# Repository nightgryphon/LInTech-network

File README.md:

# Проект по реконструкции сетевых плат ЛИнТех (IBM-PC, Корвет, УКНЦ, БК-0010)
Проект посвящен сбору информации, реконструкции и исследованию учебного сетевого комплекса LInTech для компьютерных классов СССР.

## История

Комплекс был [разработан](https://dic.academic.ru/dic.nsf/ruwiki/46187#.D0.9C.D0.BE.D0.B4.D0.B5.D1.80.D0.BD.D0.B8.D0.B7.D0.B0.D1.86.D0.B8.D1.8F) в 1990-х гг. ООО «ЛИнТех» («Лаборатория информационных технологий») совместно с ООО «Алтер-Вест»
для модернизации существующих учебных классов на базе ПЭВМ Корвет, УКНЦ и БК0010 для изучения современного на тот момент ПО для IBM PC.

Обеспечивалась работа мест учеников в режимах локальной сети и в терминальном режиме.

Наиболее интересным и необычным для того времени является **терминальный режим**, в котором существующие места учеников становятся сетевыми терминалами для головной машины на базе IBM PC. 
Поддерживаются как режимы текстового терминала для изучения MS DOS, так и графического для изучения MS Windows 3.11. 

В режиме локальной сети ученикам предоставляется доступ к дискам головной машины, причем скорость работы заметно выше штатной учебной сети. 

Комплекс упоминается в [журналах](http://school136.perm.ru/sunduk/samos/info.htm) и документах 
министерства образования и был [рекомендован](http://web.archive.org/web/20070927175919/http://www.informika.ru/text/goscom/normdoc/d_96/PRIK~5/l155.html) к применению в школах.
Однако классы на базе ПЭВМ СССР на тот момент уже активно замещались западными PC, в том числе при активной поддержке западных производителей, 
в результате комплекс LInTech не успел получить широкого распространения и был практически утрачен.

В настоящее время ученические платы изредка встречаются в ПЭВМ, списаных из школ. Чаще всего это ПЭВМ Корвет, реже УКНЦ, также известно несколько экземпляров плат для БК. 
Долгое время не удавалось разыскать сетевую плату и ПО головной машины, без которых невозможна работа ни одной из этих сетей. 
На данный момент доподлинно известно о двух сохранившихся экземплярах головной платы и, возможно, еще одном.

Первый и пока единственный публично упомянутый запуск-реконструкция сети LInTech / NET-Rt11 осуществлены [Arseny](http://uknc.narod.ru/) для ПЭВМ УКНЦ (МС 0511). 
На его сайте представлены [качественные фото плат](http://uknc.narod.ru/Img/index.htm) и [комплект учительского ПО для УКНЦ](http://uknc.narod.ru/Net-RT11/index.htm).
Однако задача реконструкции комплекса на данном этапе была существенно затруднена отсутствием копии защищенной от чтения прошивки микроконтроллера головной платы.

Второй экземпляр головной платы и бумажную документацию удалось разыскать [Serebriakov](https://github.com/paulargent). 
В 2020 году Serebriakov наладил контакты с директором ЛИнТех [Станиславом Кононовым](https://vk.com/id21313844), благодаря чему было получено сохранившееся в архивах ЛИнТех ПО и прошивки контроллера головной платы. Это решило принципиальный вопрос с прошивками и сделало возможной реконструкцию системы. Так же от Станислава было получено официальное разрешение на публикацию материалов в открытом доступе и дан зеленый свет проекту реконструкции плат.

[Night Gryphon](https://github.com/nightgryphon) удалось разыскать и восстановить клиентские платы БК0010 и УКНЦ, найти около десятка контроллеров от платы головной машины (увы, без самих плат).

Все это позволяет попробовать реконструировать и запустить сеть ЛИнТех.

## Реконструкция

Аппаратно комплекс реализован в виде клиентских плат, устанавливаемых в слоты расширения ПЭВМ учеников, и головной ISA платы для учительской IBM PC совместимой машины. 
Платы построены на основе микроконтроллеров Intel 8031 и 8051.

Связь в сети осуществляется по последовательной двухпроводной линии, что позволяет использовать существующую кабельную инфраструктуру компьютерных классов.

В качестве программного обеспечения были разработаны системы: 
- [NET-Rt11](https://www.emuverse.ru/wiki/%D0%A3%D0%9A%D0%9D%D0%A6_%D0%B6%D1%83%D1%80%D0%BD%D0%B0%D0%BB_1994-01_%D0%9B%D0%98%D0%BD%D0%A2%D0%B5%D1%85), 
- [DOS-Line](http://www.uw.ru/about/archive/dos-line/), 
- [NET-CP/M](https://oldkorvet.narod.ru/Utils.html)
- NET-БК0010

В данном проекте представлены:
- [Server-IBM-PC](./Server-IBM-PC/) - головная **[ учительская плата ISA для IBM PC ]** а так же **учительское ПО**
- [Terminal-UKNC](./Terminal-UKNC/) - клиентская плата УКНЦ
- [Terminal-BK0010](./Terminal-BK0010/) - клиентская плата БК 0010
- [Documentation](./Documentation/) - руководства

Дружественные проекты:
- [Терминал плата для ПЭВМ Корвет](https://github.com/lordamot/retro-lintech) была реконструирована коллегами NexusOfPenza и Lordamot

Платы в данном проекте не являются точной копией оригинала т.к. некоторые участки плат не видны под установлеными компонентами и невозможно сделать точную копию без разрушения оригинала. 
Реконструкция создана в KiCad с чистого листа имея оригинальную плату (или ее фото) в качестве образца. 
Не видимые элементы воссозданы путем отсмотра, прозвонки и изучения/воссоздания логики работы платы. 

Все данные публикуются с согласия представителя ЛИнТех.

## Ссылки
1. [academic.ru: Что такое УКНЦ? см раздел "Модернизация"](https://dic.academic.ru/dic.nsf/ruwiki/46187#.D0.9C.D0.BE.D0.B4.D0.B5.D1.80.D0.BD.D0.B8.D0.B7.D0.B0.D1.86.D0.B8.D1.8F)
2. [Каталог статей об УКНЦ (а также, о разработках фирмы ЛИнТех)](http://school136.perm.ru/sunduk/samos/info.htm)
3. [«NET-Rt11» — СЕТЕВАЯ СИСТЕМА ДЛЯ КУВТ «УКНЦ» С IBM-СОВМЕСТИМОЙ ГОЛОВНОЙ МАШИНОЙ](https://www.emuverse.ru/wiki/%D0%A3%D0%9A%D0%9D%D0%A6_%D0%B6%D1%83%D1%80%D0%BD%D0%B0%D0%BB_1994-01_%D0%9B%D0%98%D0%BD%D0%A2%D0%B5%D1%85)
4. [Приказ Мин Обр 'О модернизации отечественных КУВТ "Корвет" и УКНЦ' N 155/28 от 13.05.96г](http://web.archive.org/web/20070927175919/http://www.informika.ru/text/goscom/normdoc/d_96/PRIK~5/l155.html)
5. [Многозадачная, многопользовательская операционная система DOS-Line](http://www.uw.ru/about/archive/dos-line/)
6. [uknc.narod.ru: Фото от Arseny](http://uknc.narod.ru/Img/index.htm)
7. [uknc.narod.ru: оригиналы инструкции и ПО УКНЦ от Arseny](http://uknc.narod.ru/Net-RT11/index.htm)
8. [Старые фото и описание плат ЛИнТех от Serebriakov на форуме zx-pk.ru](https://zx-pk.ru/threads/2597?p=922488&viewfull=1#post922488)
9. [Образы дискет с установщиком ЛИнТех от Serebriakov на его старом сайте по Корвету oldkorvet.narod.ru)](https://oldkorvet.narod.ru/Utils.html)
10. [Дружественный проект по реконструкции платы для ПЭВМ Корвет от коллег NexusOfPenza и Lordamot](https://github.com/lordamot/retro-lintech)

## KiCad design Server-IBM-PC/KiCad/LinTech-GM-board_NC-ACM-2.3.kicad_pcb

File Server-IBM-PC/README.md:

# LInTech - плата Головной Машины (ГМ) - сервера IBM-PC

Платы реконструированы [Night Gryphon](https://night-gryphon.ru/vcard) по фото/сканам оригиналов плат, имеющихся в наличии у [Arseny](https://uknc.narod.ru/) (NC-ACM-2.2-1994) и [Serebriakov](https://github.com/PaulArgent) (NC-ACM-2.3E-1996).

В данный момент заказываются тестовые образцы платы 2.3.

Отдельное спасибо:
- [Arseny](https://uknc.narod.ru/) за исходные и дополнительные фото оригинальной платы версии NC-ACM-2.2-1994, отсмотр/поиск/прозвонку непонятных мест
- [Serebriakov](https://github.com/PaulArgent) за качественные сканы и дополнительные фото оригинальной платы версии NC-ACM-2.3E-1996.
- [Maxiol](https://forum.maxiol.com/) за помощь в воссоздании/проверке аналоговой части схемы
- Станиславу Масловски за опознание маркировки компонентов

Содержание:
- KiCad - проект реконструкции плат в формате KiCad
- LinTech-GM-board_NC-ACM-\*.pdf - реконструированые **схемы** плат 2.2 и 2.3Е
- Gerbers - **GERBER** файлы и **BOM** (списки компонентов) 
- Firmware - микропрограмма контроллера Intel 8051. Варианты для разных КУВТ и с разными лицензиями, см. README файлы.
- Reference_Photo - исходные фото, по которым велась реконструкция
- Cable - фото и схема соединительного кабеля
- [Software](./Software/) - **ПО головной машины**

Библиотека прошивок микроконтроллера платы и учительское ПО любезно предоставлены Станиславом Кононовым из ЛИнТех при содействии [Serebriakov](https://github.com/PaulArgent).

### Плата версии 2.2 
реконструирована по фото и с непосредственной помощью [Arseny](http://uknc.narod.ru/). 

### Плата версии 2.3Е
реконструирована по качественным сканам [Serebriakov](https://github.com/PaulArgent) и схеме платы 2.2. 

**Плата 2.3 имеет следующие отличия:**
- расширен блок перемычек выбора прерывания. Теперь доступны прерывания 3, 4, 7, 10, 11 (по умолчанию), 12
- светодиоды перенесены рядом с планкой и теперь видны снаружи корпуса РС, светодиод LD2 на линии "Reset" заменен на зеленый.
- добавлена возможность не запаивать не использовать часть аналоговой схемы. Добавлен подтягивающий резистор R8.
- Транзистор VT3 заменен на КТ646Б, изменены номиналы некоторых резисторов/конденсаторов.
- линия запроса прерывания вынесена из под кварцевого резонатора и добавлен земляной полигон.
- блоки перемычек заменены печатными джамперами в положении по умолчанию

На момент публикации реальные платы по данной реконструкции не изготавливались / не тестировались в железе, в проекте возможны неточности.

Реконструированые платы не являются точной копией оригинала. Положение дорожек и их форма, положение компонентов незначительно отличаются от оригинала т.к. рисовались с нуля в своей сетке с учетом современных возможностей производства и т.д. 

## Техническое описание
**[WIP]**

Плата построена на базе микроконтроллера Intel 8051 (ДД1).
 
ОЗУ контроллера расширено 573РУ10 (ДД4). Возможно размещение в этом ОЗУ как данных так и исполнение кода.
Возможна работа с микропрограммой во внешнем ПЗУ (ДД5) (требует проверки) после установки джампера Х5 в положение 2-3.

Адресное пространство контроллера разбито на 4 части по старшим битам адреса 14 и 15, что реализуется дешифратором ДД3:
- В старшей части 0xFххх расположен порт данных обмена с РС построеный на 1533ИР22 (ДД6, ДД7). 
- В адресах 0х4ххх расположено дополнительное ОЗУ
- В адресах 0х0ххх (предположительно) может быть установлено ПЗУ с внешней микропрограммой (ДД5)

При получении данных от РС в порт данных - выдается прерывание Int0 (триггер ДД13-А). Младший бит адреса порта данных, в который производилась запись, может быть прочитан из порта Р3 бит 4.

При чтении РС из порта данных выдается прерывание Int1 (триггер ДД13-Б)

Для запроса прерывания на РС необходимо записать "1" в порт Р3 бит 5.

При перезагрузке РС по сигналу RESET на шине ISA микроконтроллер так же переводится в ресет до снятия бита ресета со стороны РС записью "0" в бит 7 порта управления.

Обмен с линией осуществляется через последовательный порт RXD/TXD.

### Интерфейс PC
Базовый адрес портов В/В выбирается перемычками SA.1-7 которые соответствуют битам 3-9 адреса порта.

По умолчанию:
0x0120, 0х0121 - порт данных (Port 67: ДД6, ДД7)
0x0122 - порт статуса и управления (Port 89: ДД8, ДД9)

Чтение:
	3 - "1" = поступили данные от контроллера
	4 - "1" = порт данных свободен, данные прочитаны контроллером
	5 - контроллер выход T1/Port3.5
	6 - "1" = разрешено прерывание
	7 - перемычка SA.8

Запись
	6 - "1" = разрешить прерывание
	7 - ресет контроллера. После перезагрузки PC контроллер находится в ресете и надо записать "0" в этот бит для старта платы.

Прерывание 11 (может быть изменено перемычками IRQ) - выход MCU Port3 bit 4, со стороны PC разрешается записью "1" в бит 6 регистра управления.

Известные проблемы платы:
- при использовании прерывания ISA у некоторых экземпляров платы происходили его ложные срабатывания/помехи вплоть до "завешивания" РС. 
Предположительно связано с разводкой линии прерывания на плате версии 2.2. В плате версии 2.3 это было изменено.

### Описание микропрограммы
[Требуется помощь]

## Сетевой протокол
[Требуется помощь]

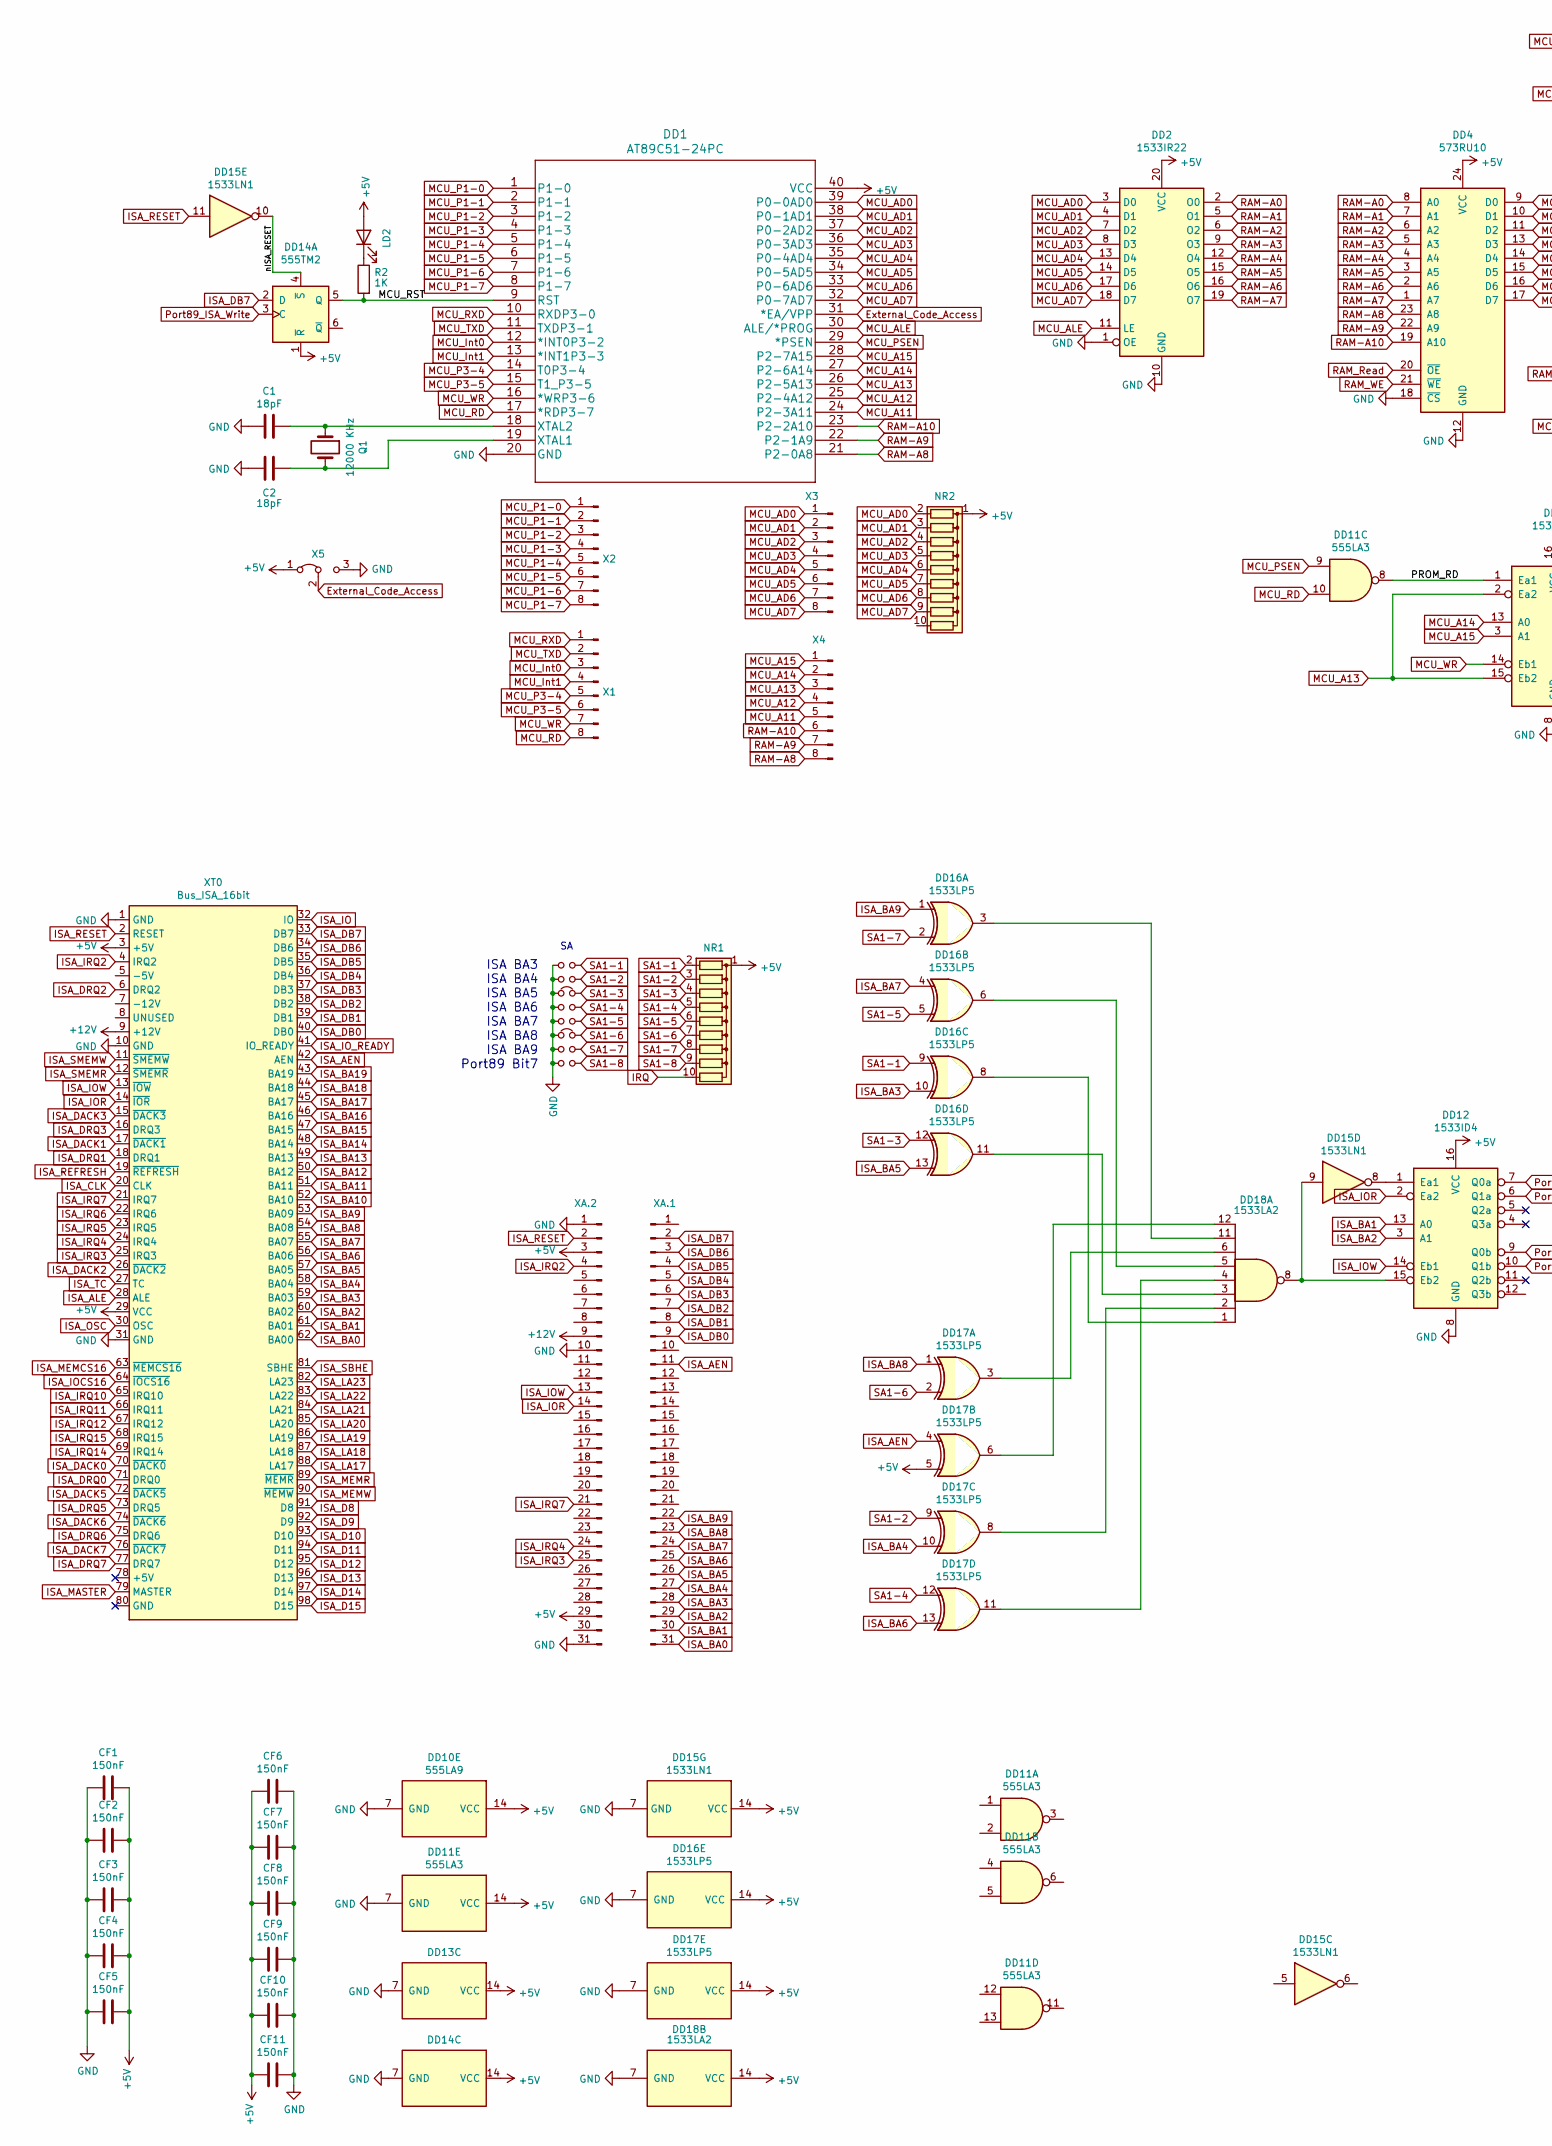
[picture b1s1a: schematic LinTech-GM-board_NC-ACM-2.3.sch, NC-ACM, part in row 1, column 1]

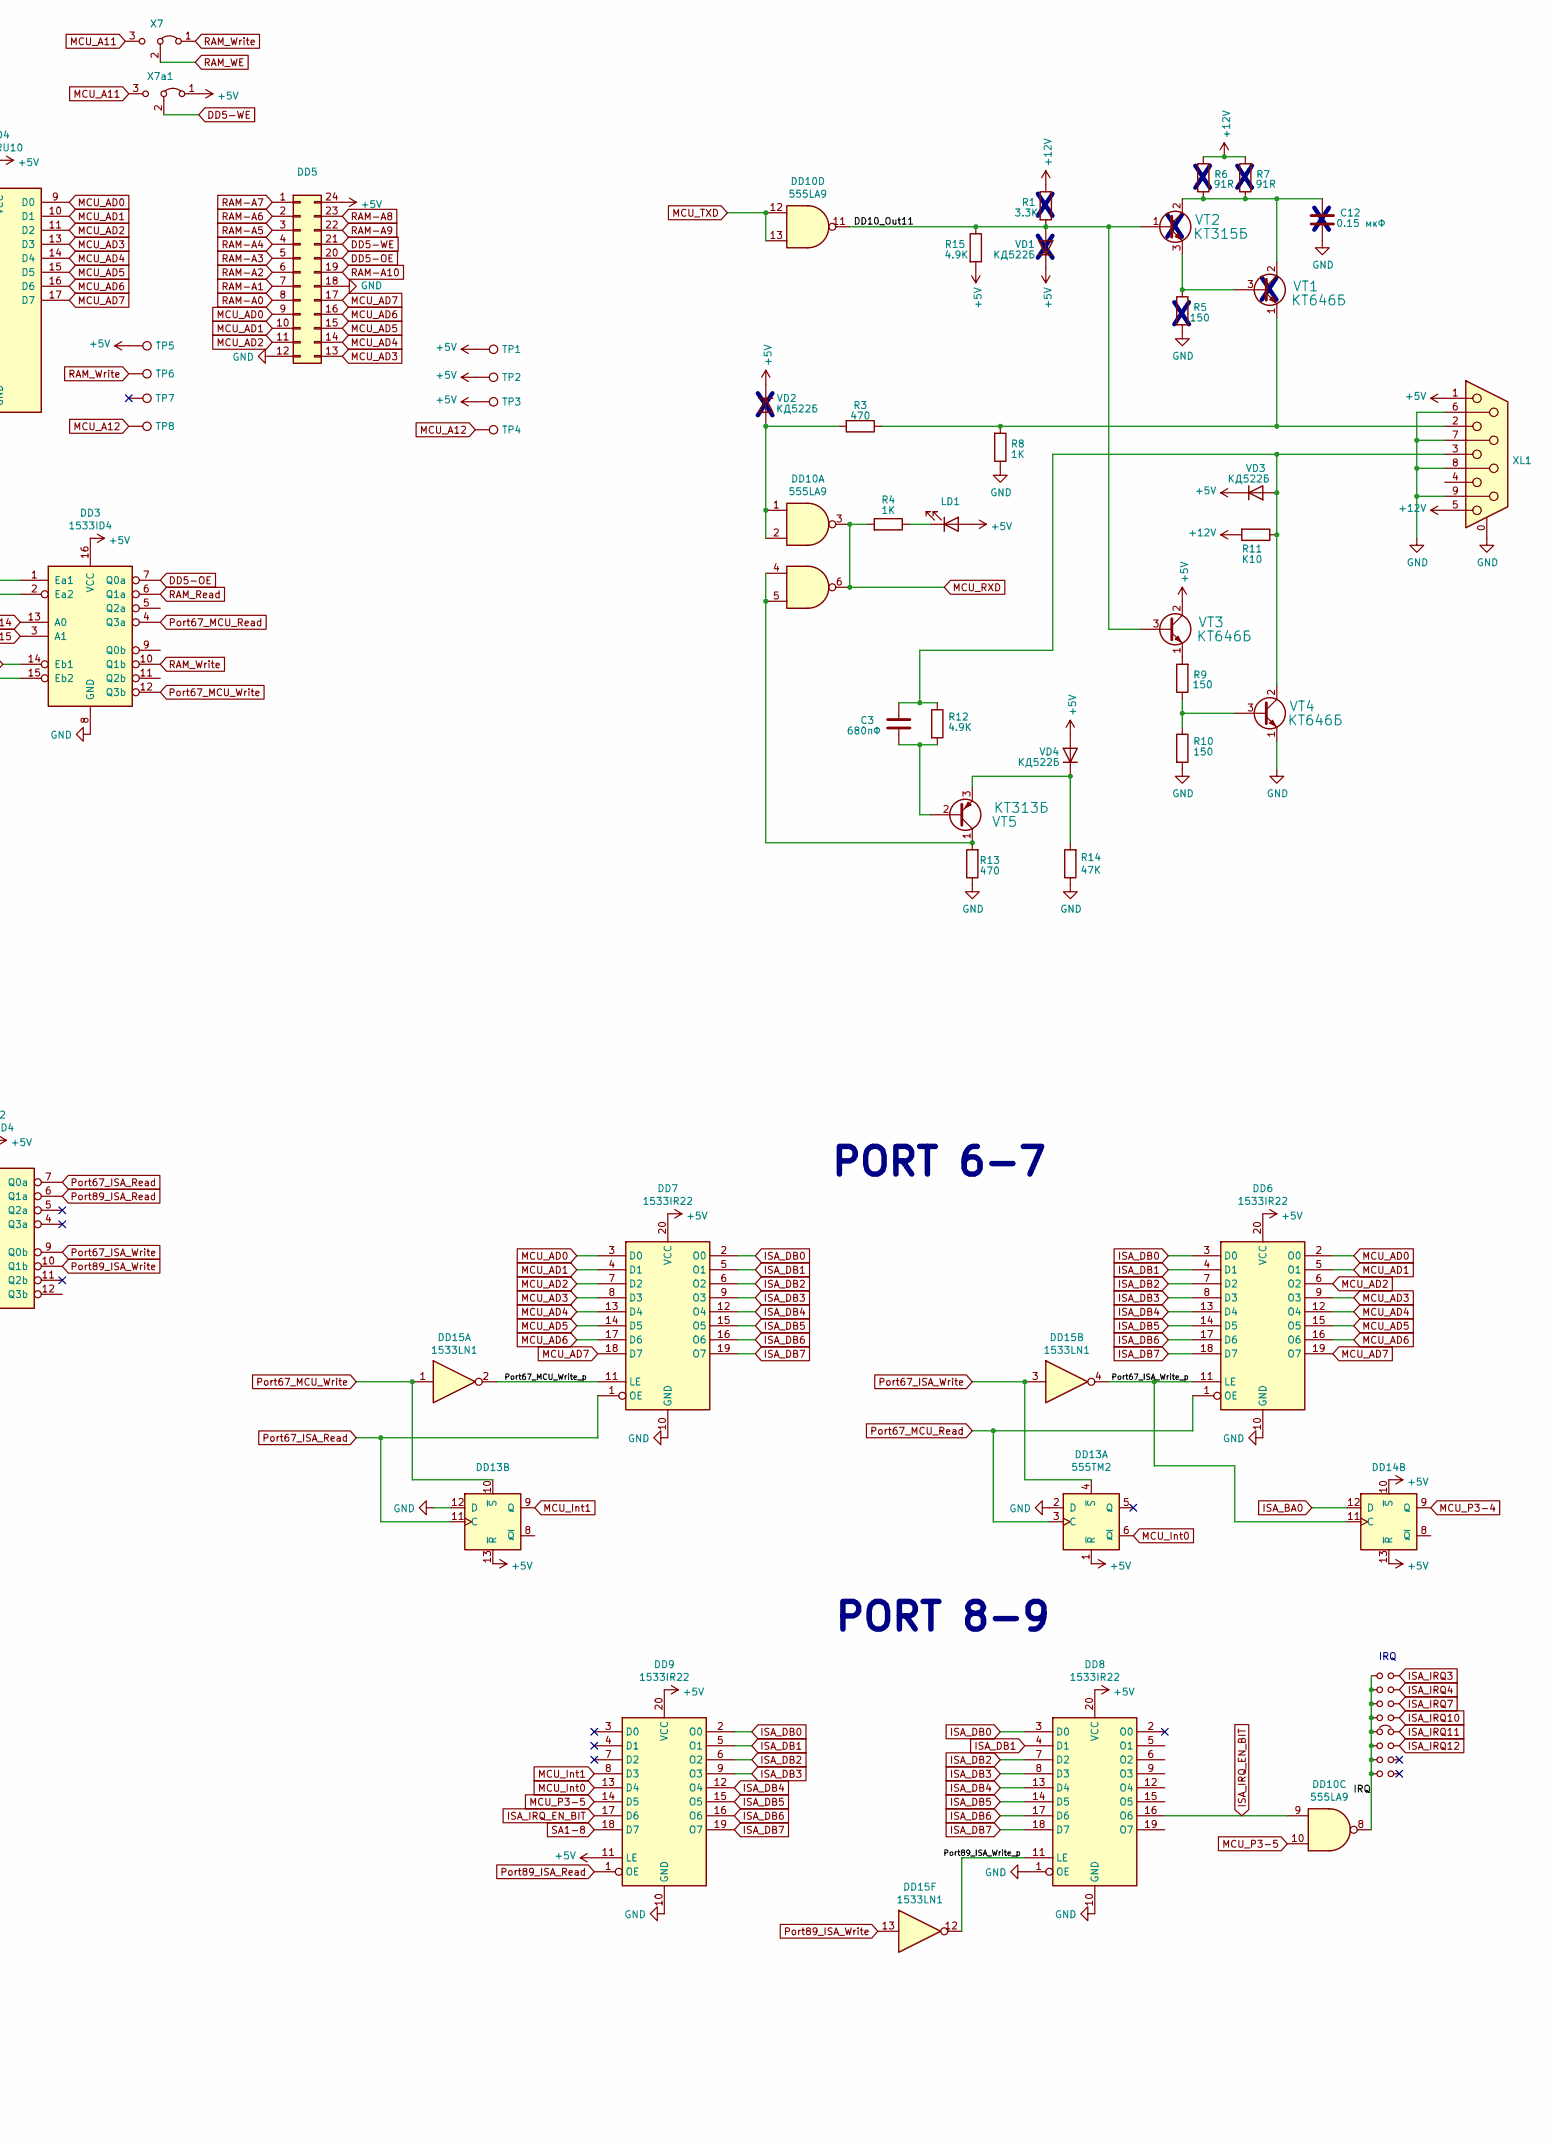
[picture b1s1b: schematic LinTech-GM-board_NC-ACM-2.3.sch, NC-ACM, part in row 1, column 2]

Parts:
C1, C2: 18pF; C_Disc_D5.0mm_W2.5mm_P5.00mm
C3: 680пФ; C_Disc_D5.0mm_W2.5mm_P5.00mm
C12: 0.15 мкФ; C_Disc_D5.0mm_W2.5mm_P5.00mm
CF1, CF2, CF3, CF4, CF5, CF6, CF7, CF8, CF9, CF10, CF11: 150nF; C_Disc_D5.0mm_W2.5mm_P5.00mm
DD1: AT89C51-24PC; DIP-40_W15.24mm
DD2, DD6, DD7, DD8, DD9: 1533IR22; DIP-20_W7.62mm
DD3, DD12: 1533ID4; DIP-16_W7.62mm
DD4: 573RU10; DIP-24_W15.24mm
DD5: Socket DIP24; DIP-24_W15.24mm_Socket
DD10: 555LA9; DIP-14_W7.62mm
DD11: 555LA3; DIP-14_W7.62mm
DD13, DD14: 555TM2; DIP-14_W7.62mm
DD15: 1533LN1; DIP-14_W7.62mm
DD16, DD17: 1533LP5; DIP-14_W7.62mm
DD18: 1533LA2; DIP-14_W7.62mm
LD1: LED Red 4mm; LED_D4.0mm
LD2: LED Green 4mm; LED_D4.0mm
NR1: 3.3K ?; R_Array_SIP10
NR2: R_Array_SIP10
Q1: 12000 KHz; Crystal_HC18-U_Horizontal
R1: 3.3K; R_Axial_DIN0309_L9.0mm_D3.2mm_P12.70mm_Horizontal
R2, R4, R8: 1K; R_Axial_DIN0309_L9.0mm_D3.2mm_P12.70mm_Horizontal
R3, R13: 470; R_Axial_DIN0309_L9.0mm_D3.2mm_P12.70mm_Horizontal
R5, R9, R10: 150; R_Axial_DIN0309_L9.0mm_D3.2mm_P12.70mm_Horizontal
R6, R7: 91R; R_Axial_DIN0918_L18.0mm_D9.0mm_P22.86mm_Horizontal
R11: K10; R_Axial_DIN0918_L18.0mm_D9.0mm_P22.86mm_Horizontal
R12, R15: 4.9K; R_Axial_DIN0309_L9.0mm_D3.2mm_P12.70mm_Horizontal
R14: 47K; R_Axial_DIN0309_L9.0mm_D3.2mm_P12.70mm_Horizontal
SAjp1, SAjp2, SAjp4, SAjp5, SAjp7, SAjp8, SAjp9, SAjp10, SAjp11, SAjp12, SAjp14, SAjp15, SAjp16: Jumper_P2.54mm_Open
SAjp3, SAjp6, SAjp13: Jumper_P2.54mm_Close
TP1, TP2, TP3, TP4, TP5, TP6, TP7, TP8: TestPoint; TestPad
VD1, VD2, VD3, VD4: КД522Б; D_A-405_P12.70mm_Horizontal
VT1, VT3, VT4: КТ646Б; TO-126-3_Vertical
VT2: КТ315Б; TO-92S_Wide
VT5: КТ313Б; TO-92
X1, X2, X3, X4: PinHeader_1x08_P2.54mm_Vertical
X5: PinHeader_1x03_P2.54mm_Vertical
X7, X7a1: Conn_02x03_Counter_Clockwise; Jumper3_12closed_P2.54mm
XA.1, XA.2: PinHeader_1x31_P2.54mm_Vertical
XL1: DB9_Female; DSUB-9_Female_Horizontal_P2.77x2.84mm_EdgePinOffset7.70mm_H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
XT0: Bus_ISA_16bit; BUS_AT

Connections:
+5V: CF1.2, CF2.1, CF3.2, CF4.2, CF5.1, CF6.2, CF7.2, CF8.1, CF9.2, CF10.2, CF11.2, DD1.40 (VCC), DD2.20 (VCC), DD3.16 (VCC), DD4.24 (VCC), DD5.24, DD6.20 (VCC), DD7.20 (VCC), DD8.20 (VCC), DD9.11 (LE), DD9.20 (VCC), DD10.14 (VCC), DD11.14 (VCC), DD12.16 (VCC), DD13.1 (~R), DD13.13 (~R), DD13.14 (VCC), DD14.1 (~R), DD14.10 (~S), DD14.13 (~R), DD14.14 (VCC), DD15.14 (VCC), DD16.14 (VCC), DD17.5, DD17.14 (VCC), DD18.14 (VCC), LD1.2 (A), LD2.2 (A), NR1.1 (common), NR2.1 (common), R15.2, TP1.1, TP2.1, TP3.1, TP5.1, VD1.1 (K), VD2.1 (K), VD3.1 (K), VD4.2 (A), VT3.2 (C), X5.1 (A), X7a1.1 (A), XA.2.3, XA.2.29, XL1.1, XT0.3 (+5V), XT0.29 (VCC)
+12V: R1.1, R6.2, R7.2, R11.2, XA.2.9, XL1.5, XT0.9 (+12V)
/DD10_Out11: DD10.11, R1.2, R15.1, VD1.2 (A), VT2.1 (B), VT3.3 (B)
/MCU_RST: DD1.9 (RST), DD14.5 (Q), R2.2
/PROM_RD: DD3.1 (Ea1), DD11.8
/Port67_ISA_Write_p: DD6.11 (LE), DD14.11 (C), DD15.4
/Port67_MCU_Write_p: DD7.11 (LE), DD15.2
/Port89_ISA_Write_p: DD8.11 (LE), DD15.12
/nISA_RESET: DD14.4 (~S), DD15.10
DD5-OE: DD3.7 (Q0a), DD5.20
DD5-WE: DD5.21, X7a1.2 (C)
External_Code_Access: DD1.31 (*EA/VPP), X5.2 (C)
GND: C1.2, C2.1, C12.2, CF1.1, CF2.2, CF3.1, CF4.1, CF5.2, CF6.1, CF7.1, CF8.2, CF9.1, CF10.1, CF11.1, DD1.20 (GND), DD2.1 (OE), DD2.10 (GND), DD3.8 (GND), DD4.12 (GND), DD4.18 (~CS), DD5.12, DD5.18, DD6.10 (GND), DD7.10 (GND), DD8.1 (OE), DD8.10 (GND), DD9.10 (GND), DD10.7 (GND), DD11.7 (GND), DD12.8 (GND), DD13.2 (D), DD13.7 (GND), DD13.12 (D), DD14.7 (GND), DD15.7 (GND), DD16.7 (GND), DD17.7 (GND), DD18.7 (GND), R5.2, R8.1, R10.2, R13.1, R14.1, SAjp1.1, SAjp2.1, SAjp3.1, SAjp4.1, SAjp5.1, SAjp6.1, SAjp7.1, SAjp8.1, VT4.1 (E), X5.3 (B), XA.2.1, XA.2.10, XA.2.31, XL1.0 (PAD), XL1.6, XL1.7, XL1.8, XL1.9, XT0.1 (GND), XT0.10 (GND), XT0.31 (GND)
IRQ: DD10.8, NR1.10 (R9), SAjp9.1, SAjp10.1, SAjp11.1, SAjp12.1, SAjp13.1, SAjp14.1, SAjp15.1, SAjp16.1
ISA_AEN: DD17.4, XA.1.11, XT0.42 (AEN)
ISA_ALE: XT0.28 (ALE)
ISA_BA0: DD14.12 (D), XA.1.31, XT0.62 (BA00)
ISA_BA1: DD12.13 (A0), XA.1.30, XT0.61 (BA01)
ISA_BA2: DD12.3 (A1), XA.1.29, XT0.60 (BA02)
ISA_BA3: DD16.10, XA.1.28, XT0.59 (BA03)
ISA_BA4: DD17.10, XA.1.27, XT0.58 (BA04)
ISA_BA5: DD16.13, XA.1.26, XT0.57 (BA05)
ISA_BA6: DD17.13, XA.1.25, XT0.56 (BA06)
ISA_BA7: DD16.4, XA.1.24, XT0.55 (BA07)
ISA_BA8: DD17.1, XA.1.23, XT0.54 (BA08)
ISA_BA9: DD16.1, XA.1.22, XT0.53 (BA09)
ISA_BA10: XT0.52 (BA10)
ISA_BA11: XT0.51 (BA11)
ISA_BA12: XT0.50 (BA12)
ISA_BA13: XT0.49 (BA13)
ISA_BA14: XT0.48 (BA14)
ISA_BA15: XT0.47 (BA15)
ISA_BA16: XT0.46 (BA16)
ISA_BA17: XT0.45 (BA17)
ISA_BA18: XT0.44 (BA18)
ISA_BA19: XT0.43 (BA19)
ISA_CLK: XT0.20 (CLK)
ISA_D8: XT0.91 (D8)
ISA_D9: XT0.92 (D9)
ISA_D10: XT0.93 (D10)
ISA_D11: XT0.94 (D11)
ISA_D12: XT0.95 (D12)
ISA_D13: XT0.96 (D13)
ISA_D14: XT0.97 (D14)
ISA_D15: XT0.98 (D15)
ISA_DACK0: XT0.70 (~DACK0)
ISA_DACK1: XT0.17 (~DACK1)
ISA_DACK2: XT0.26 (~DACK2)
ISA_DACK3: XT0.15 (~DACK3)
ISA_DACK5: XT0.72 (~DACK5)
ISA_DACK6: XT0.74 (~DACK6)
ISA_DACK7: XT0.76 (~DACK7)
ISA_DB0: DD6.3 (D0), DD7.2 (O0), DD8.3 (D0), DD9.2 (O0), XA.1.9, XT0.40 (DB0)
ISA_DB1: DD6.4 (D1), DD7.5 (O1), DD8.4 (D1), DD9.5 (O1), XA.1.8, XT0.39 (DB1)
ISA_DB2: DD6.7 (D2), DD7.6 (O2), DD8.7 (D2), DD9.6 (O2), XA.1.7, XT0.38 (DB2)
ISA_DB3: DD6.8 (D3), DD7.9 (O3), DD8.8 (D3), DD9.9 (O3), XA.1.6, XT0.37 (DB3)
ISA_DB4: DD6.13 (D4), DD7.12 (O4), DD8.13 (D4), DD9.12 (O4), XA.1.5, XT0.36 (DB4)
ISA_DB5: DD6.14 (D5), DD7.15 (O5), DD8.14 (D5), DD9.15 (O5), XA.1.4, XT0.35 (DB5)
ISA_DB6: DD6.17 (D6), DD7.16 (O6), DD8.17 (D6), DD9.16 (O6), XA.1.3, XT0.34 (DB6)
ISA_DB7: DD6.18 (D7), DD7.19 (O7), DD8.18 (D7), DD9.19 (O7), DD14.2 (D), XA.1.2, XT0.33 (DB7)
ISA_DRQ0: XT0.71 (DRQ0)
ISA_DRQ1: XT0.18 (DRQ1)
ISA_DRQ2: XT0.6 (DRQ2)
ISA_DRQ3: XT0.16 (DRQ3)
ISA_DRQ5: XT0.73 (DRQ5)
ISA_DRQ6: XT0.75 (DRQ6)
ISA_DRQ7: XT0.77 (DRQ7)
ISA_IO: XT0.32 (IO)
ISA_IOCS16: XT0.64 (~IOCS16)
ISA_IOR: DD12.2 (Ea2), XA.2.14, XT0.14 (~IOR)
ISA_IOW: DD12.14 (Eb1), XA.2.13, XT0.13 (~IOW)
ISA_IO_READY: XT0.41 (IO_READY)
ISA_IRQ2: XA.2.4, XT0.4 (IRQ2)
ISA_IRQ3: SAjp9.2, XA.2.25, XT0.25 (IRQ3)
ISA_IRQ4: SAjp10.2, XA.2.24, XT0.24 (IRQ4)
ISA_IRQ5: XT0.23 (IRQ5)
ISA_IRQ6: XT0.22 (IRQ6)
ISA_IRQ7: SAjp11.2, XA.2.21, XT0.21 (IRQ7)
ISA_IRQ10: SAjp12.2, XT0.65 (IRQ10)
ISA_IRQ11: SAjp13.2, XT0.66 (IRQ11)
ISA_IRQ12: SAjp14.2, XT0.67 (IRQ12)
ISA_IRQ14: XT0.69 (IRQ14)
ISA_IRQ15: XT0.68 (IRQ15)
ISA_IRQ_EN_BIT: DD8.16 (O6), DD9.17 (D6), DD10.9
ISA_LA17: XT0.88 (LA17)
ISA_LA18: XT0.87 (LA18)
ISA_LA19: XT0.86 (LA19)
ISA_LA20: XT0.85 (LA20)
ISA_LA21: XT0.84 (LA21)
ISA_LA22: XT0.83 (LA22)
ISA_LA23: XT0.82 (LA23)
ISA_MASTER: XT0.79 (MASTER)
ISA_MEMCS16: XT0.63 (~MEMCS16)
ISA_MEMR: XT0.89 (~MEMR)
ISA_MEMW: XT0.90 (~MEMW)
ISA_OSC: XT0.30 (OSC)
ISA_REFRESH: XT0.19 (~REFRESH)
ISA_RESET: DD15.11, XA.2.2, XT0.2 (RESET)
ISA_SBHE: XT0.81 (SBHE)
ISA_SMEMR: XT0.12 (~SMEMR)
ISA_SMEMW: XT0.11 (~SMEMW)
ISA_TC: XT0.27 (TC)
MCU_A11: DD1.24 (P2-3A11), X4.5, X7.3 (B), X7a1.3 (B)
MCU_A12: DD1.25 (P2-4A12), TP4.1, TP8.1, X4.4
MCU_A13: DD1.26 (P2-5A13), DD3.2 (Ea2), DD3.15 (Eb2), X4.3
MCU_A14: DD1.27 (P2-6A14), DD3.13 (A0), X4.2
MCU_A15: DD1.28 (P2-7A15), DD3.3 (A1), X4.1
MCU_AD0: DD1.39 (P0-0AD0), DD2.3 (D0), DD4.9 (D0), DD5.9, DD6.2 (O0), DD7.3 (D0), NR2.2 (R1), X3.1
MCU_AD1: DD1.38 (P0-1AD1), DD2.4 (D1), DD4.10 (D1), DD5.10, DD6.5 (O1), DD7.4 (D1), NR2.3 (R2), X3.2
MCU_AD2: DD1.37 (P0-2AD2), DD2.7 (D2), DD4.11 (D2), DD5.11, DD6.6 (O2), DD7.7 (D2), NR2.4 (R3), X3.3
MCU_AD3: DD1.36 (P0-3AD3), DD2.8 (D3), DD4.13 (D3), DD5.13, DD6.9 (O3), DD7.8 (D3), NR2.5 (R4), X3.4
MCU_AD4: DD1.35 (P0-4AD4), DD2.13 (D4), DD4.14 (D4), DD5.14, DD6.12 (O4), DD7.13 (D4), NR2.6 (R5), X3.5
MCU_AD5: DD1.34 (P0-5AD5), DD2.14 (D5), DD4.15 (D5), DD5.15, DD6.15 (O5), DD7.14 (D5), NR2.7 (R6), X3.6
MCU_AD6: DD1.33 (P0-6AD6), DD2.17 (D6), DD4.16 (D6), DD5.16, DD6.16 (O6), DD7.17 (D6), NR2.8 (R7), X3.7
MCU_AD7: DD1.32 (P0-7AD7), DD2.18 (D7), DD4.17 (D7), DD5.17, DD6.19 (O7), DD7.18 (D7), NR2.9 (R8), X3.8
MCU_ALE: DD1.30 (ALE/*PROG), DD2.11 (LE)
MCU_Int0: DD1.12 (*INT0P3-2), DD9.13 (D4), DD13.6 (~Q), X1.3
MCU_Int1: DD1.13 (*INT1P3-3), DD9.8 (D3), DD13.9 (Q), X1.4
MCU_P1-0: DD1.1 (P1-0), X2.1
MCU_P1-1: DD1.2 (P1-1), X2.2
MCU_P1-2: DD1.3 (P1-2), X2.3
MCU_P1-3: DD1.4 (P1-3), X2.4
MCU_P1-4: DD1.5 (P1-4), X2.5
MCU_P1-5: DD1.6 (P1-5), X2.6
MCU_P1-6: DD1.7 (P1-6), X2.7
MCU_P1-7: DD1.8 (P1-7), X2.8
MCU_P3-4: DD1.14 (T0P3-4), DD14.9 (Q), X1.5
MCU_P3-5: DD1.15 (T1_P3-5), DD9.14 (D5), DD10.10, X1.6
MCU_PSEN: DD1.29 (*PSEN), DD11.9
MCU_RD: DD1.17 (*RDP3-7), DD11.10, X1.8
MCU_RXD: DD1.10 (RXDP3-0), DD10.3, DD10.6, R4.2, X1.1
MCU_TXD: DD1.11 (TXDP3-1), DD10.12, DD10.13, X1.2
MCU_WR: DD1.16 (*WRP3-6), DD3.14 (Eb1), X1.7
unnamed: C1.1, DD1.18 (XTAL2), Q1.1
unnamed: C2.2, DD1.19 (XTAL1), Q1.2
unnamed: C3.1, R11.1, R12.1, VD3.2 (A), VT4.2 (C), XL1.3
unnamed: C3.2, R12.2, VT5.2 (B)
unnamed: C12.1, R6.1, R7.1, VT1.2 (C), VT2.2 (C)
unnamed: DD10.1, DD10.2, R3.2, VD2.2 (A)
unnamed: DD10.4, DD10.5, R13.2, VT5.1 (C)
unnamed: DD12.1 (Ea1), DD15.8
unnamed: DD12.15 (Eb2), DD15.9, DD18.8
unnamed: DD16.3, DD18.11
unnamed: DD16.6, DD18.5
unnamed: DD16.8, DD18.1
unnamed: DD16.11, DD18.3
unnamed: DD17.3, DD18.6
unnamed: DD17.6, DD18.12
unnamed: DD17.8, DD18.2
unnamed: DD17.11, DD18.4
unnamed: LD1.1 (K), R4.1
unnamed: LD2.1 (K), R2.1
unnamed: R3.1, R8.2, VT1.1 (E), XL1.2
unnamed: R5.1, VT1.3 (B), VT2.3 (E)
unnamed: R9.2, VT3.1 (E)
unnamed: R9.1, R10.1, VT4.3 (B)
unnamed: R14.2, VD4.1 (K), VT5.3 (E)
Port67_ISA_Read: DD7.1 (OE), DD12.7 (Q0a), DD13.11 (C)
Port67_ISA_Write: DD12.9 (Q0b), DD13.4 (~S), DD15.3
Port67_MCU_Read: DD3.4 (Q3a), DD6.1 (OE), DD13.3 (C)
Port67_MCU_Write: DD3.12 (Q3b), DD13.10 (~S), DD15.1
Port89_ISA_Read: DD9.1 (OE), DD12.6 (Q1a)
Port89_ISA_Write: DD12.10 (Q1b), DD14.3 (C), DD15.13
RAM-A0: DD2.2 (O0), DD4.8 (A0), DD5.8
RAM-A1: DD2.5 (O1), DD4.7 (A1), DD5.7
RAM-A2: DD2.6 (O2), DD4.6 (A2), DD5.6
RAM-A3: DD2.9 (O3), DD4.5 (A3), DD5.5
RAM-A4: DD2.12 (O4), DD4.4 (A4), DD5.4
RAM-A5: DD2.15 (O5), DD4.3 (A5), DD5.3
RAM-A6: DD2.16 (O6), DD4.2 (A6), DD5.2
RAM-A7: DD2.19 (O7), DD4.1 (A7), DD5.1
RAM-A8: DD1.21 (P2-0A8), DD4.23 (A8), DD5.23, X4.8
RAM-A9: DD1.22 (P2-1A9), DD4.22 (A9), DD5.22, X4.7
RAM-A10: DD1.23 (P2-2A10), DD4.19 (A10), DD5.19, X4.6
RAM_Read: DD3.6 (Q1a), DD4.20 (~OE)
RAM_WE: DD4.21 (~WE), X7.2 (C)
RAM_Write: DD3.10 (Q1b), TP6.1, X7.1 (A)
SA1-1: DD16.9, NR1.2 (R1), SAjp1.2
SA1-2: DD17.9, NR1.3 (R2), SAjp2.2
SA1-3: DD16.12, NR1.4 (R3), SAjp3.2
SA1-4: DD17.12, NR1.5 (R4), SAjp4.2
SA1-5: DD16.5, NR1.6 (R5), SAjp5.2
SA1-6: DD17.2, NR1.7 (R6), SAjp6.2
SA1-7: DD16.2, NR1.8 (R7), SAjp7.2
SA1-8: DD9.18 (D7), NR1.9 (R8), SAjp8.2

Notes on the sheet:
PORT 8-9
PORT 6-7
ISA BA3 ISA BA4 ISA BA5 ISA BA6 ISA BA7 ISA BA8 ISA BA9 Port89 Bit7
IRQ

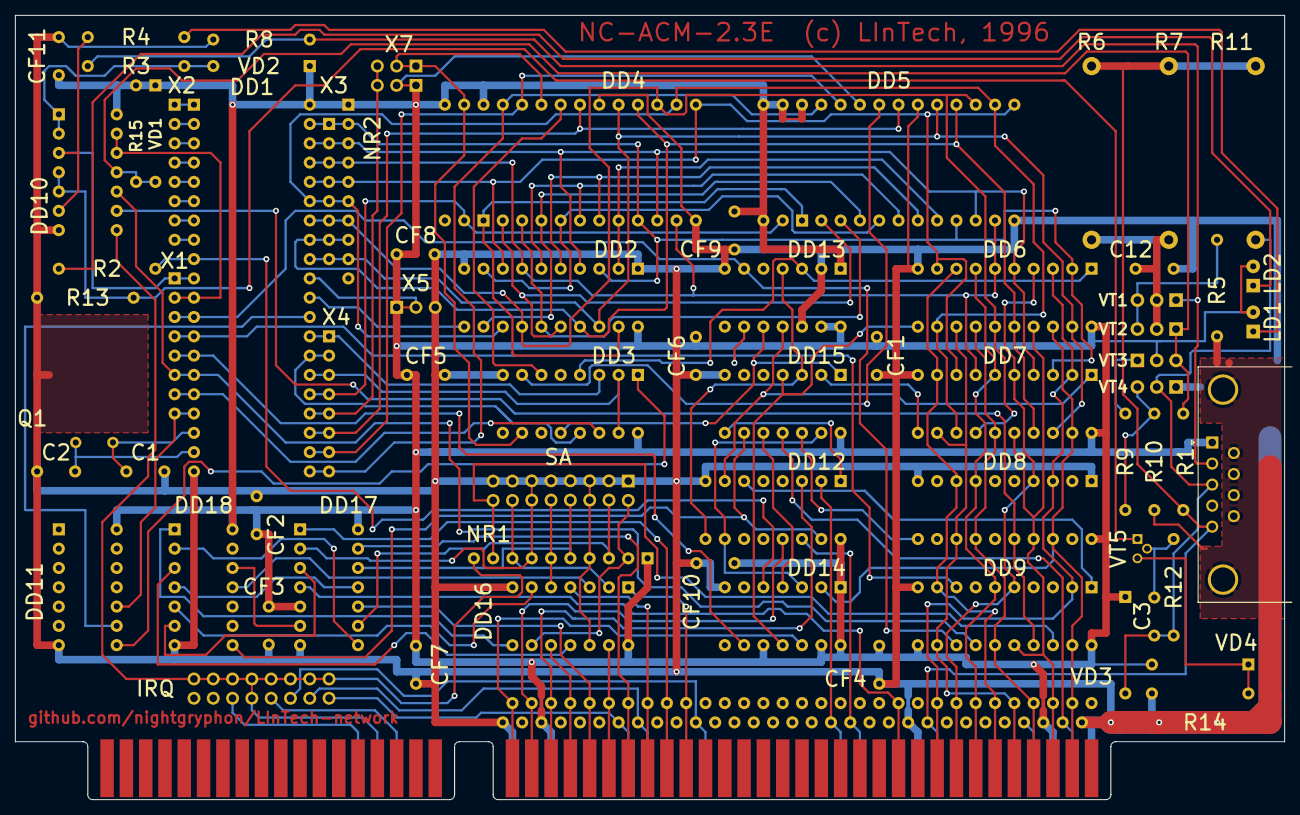
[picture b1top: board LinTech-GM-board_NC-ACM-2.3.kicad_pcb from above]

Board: 2 copper layers, 167.0 x 103.2 mm, 97 parts (0 on the bottom side), 127 nets.

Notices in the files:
Terminal-UKNC/KiCad/LinTech-UKNC-board.kicad_pcb:
(c)1994
